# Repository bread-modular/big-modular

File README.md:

# Big Modular

A collection of Eurorack modules built with shared KiCad tooling.

## Modules

| Module | Description | Release |
| --- | --- | --- |
| [`usb-power`](modules/usb-power/) | USB-C PD input → protected 9V, dual TPS54302 bucks, TPS65131 raw ±13.5V, TPS7A4700/TPS7A3301 quiet ±12V, +5V | LDO-R1 source; recovered exports STALE |

Each module is self-contained under `modules/<name>/`:

```text
modules/usb-power/
  hardware/     KiCad project (usb-power.kicad_{pro,sch,pcb}, panel, local libs)
  docs/         design, fabrication and evidence notes
  tools/        module generators/checkers
  tests/        module regression tests
  jlcpcb/       recovered Gerber/BOM/CPL snapshot (STALE until re-export)
```

## Common tooling

`opt/` holds shared, module-independent tooling and must not be copied into modules:

- `opt/kicad-tools/` — native KiCad checks, PCB/schematic edits, JLCPCB export/assembly
- `opt/kicad-routing/` — optional router facade

Read `opt/kicad-tools/skills/kicad-workflow/SKILL.md` and
`opt/kicad-tools/skills/jlcpcb-assembly/SKILL.md` before KiCad or sourcing work.

## Quick check

```sh
python3 -B opt/kicad-tools/kicad_tools.py doctor --config modules/usb-power/tools/kicad-project.json
python3 -B -m unittest discover -s modules/usb-power/tests -v
```

Recovery evidence and remaining release gates: [`modules/usb-power/docs/migration-recovery.md`](modules/usb-power/docs/migration-recovery.md).

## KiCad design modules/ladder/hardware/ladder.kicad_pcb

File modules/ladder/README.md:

# LADDER: analog 16bit ladder filter + envelope + vactrol VCA

An analog take on the modules/16bit polysynth ladder filter: a classic Moog 4-pole
transistor ladder with the 16bit's controls and its resonance makeup (the dry level holds as
resonance goes up), an ATtiny1616 envelope driven by GATE or MIDI, a full CV bypass, and a
Bread Modular V2CA-style vactrol VCA on the filter output.

| Control / jack | Function |
|---|---|
| **CUTOFF** | ~55 Hz .. ~17 kHz, exponential, CW = open |
| **RESONANCE** | vactrol-controlled, 0 .. self-oscillation near the top (point depends on the vactrol); dry level kept (16bit (1 + k) makeup) |
| **ENV TIME** | attack = release, 5 ms .. 2 s (firmware) |
| **DEPTH** | 0 .. +8 octaves of envelope (or CV) on top of CUTOFF (read by the MCU, recordable) |
| **REC** + LED | records ENV TIME + DEPTH for 4 bars on MIDI clock, then loops (as ACID; firmware to write) |
| **CURVE** | VCA response: CCW punchy, CW soft (V2CA CURVE) |
| **MIDI**, **GATE** | start / release the envelope (MIDI: TS, JP1 protected / direct) |
| **CV** | 0..5 V, replaces the envelope (cutoff via the MCU x DEPTH; the VCA directly) |
| **AUDIO IN** | 10 Vpp |
| **RES CV** | adds to RESONANCE (slow, through the vactrol), +5 V ~ the knob's full range |
| **FILTER OUT**, **VCA OUT** | direct ladder out; through the vactrol VCA |

**Status: S3 schematic (vactrol resonance, REC; ERC 0, netlist asserted) + R2 routed carrier: 10HP,
4 layers, all SMD on the back (manual routing + 2026-11-10 fab-review fixes; DRC 0 / unconnected 0 /
parity 0). Panel PCB + printable panel. JLCPCB export in [`jlcpcb/`](jlcpcb/README.md), not
supplier-accepted, not built. No firmware.**

Panel, top to bottom: MIDI, GATE, CV, RES CV; CUTOFF, RES; ENV TIME, DEPTH; REC button + LED,
CURVE; AUDIO IN, FILTER OUT, VCA OUT.

```sh
python3 -B tools/build_schematic.py   # schematic (placement by hand, wires by its router)
python3 -B tools/build_layout.py      # carrier P2 placement + panel (refuses a routed carrier: do not run)
python3 -B tools/sim_ladder.py        # ngspice check of ladder / expo / resonance
kicad-cli sch erc --severity-all --format json -o research/erc.json hardware/ladder.kicad_sch
```

Schematic PDF: [`docs/ladder-schematic.pdf`](docs/ladder-schematic.pdf). Design notes:
[`docs/research.md`](docs/research.md).

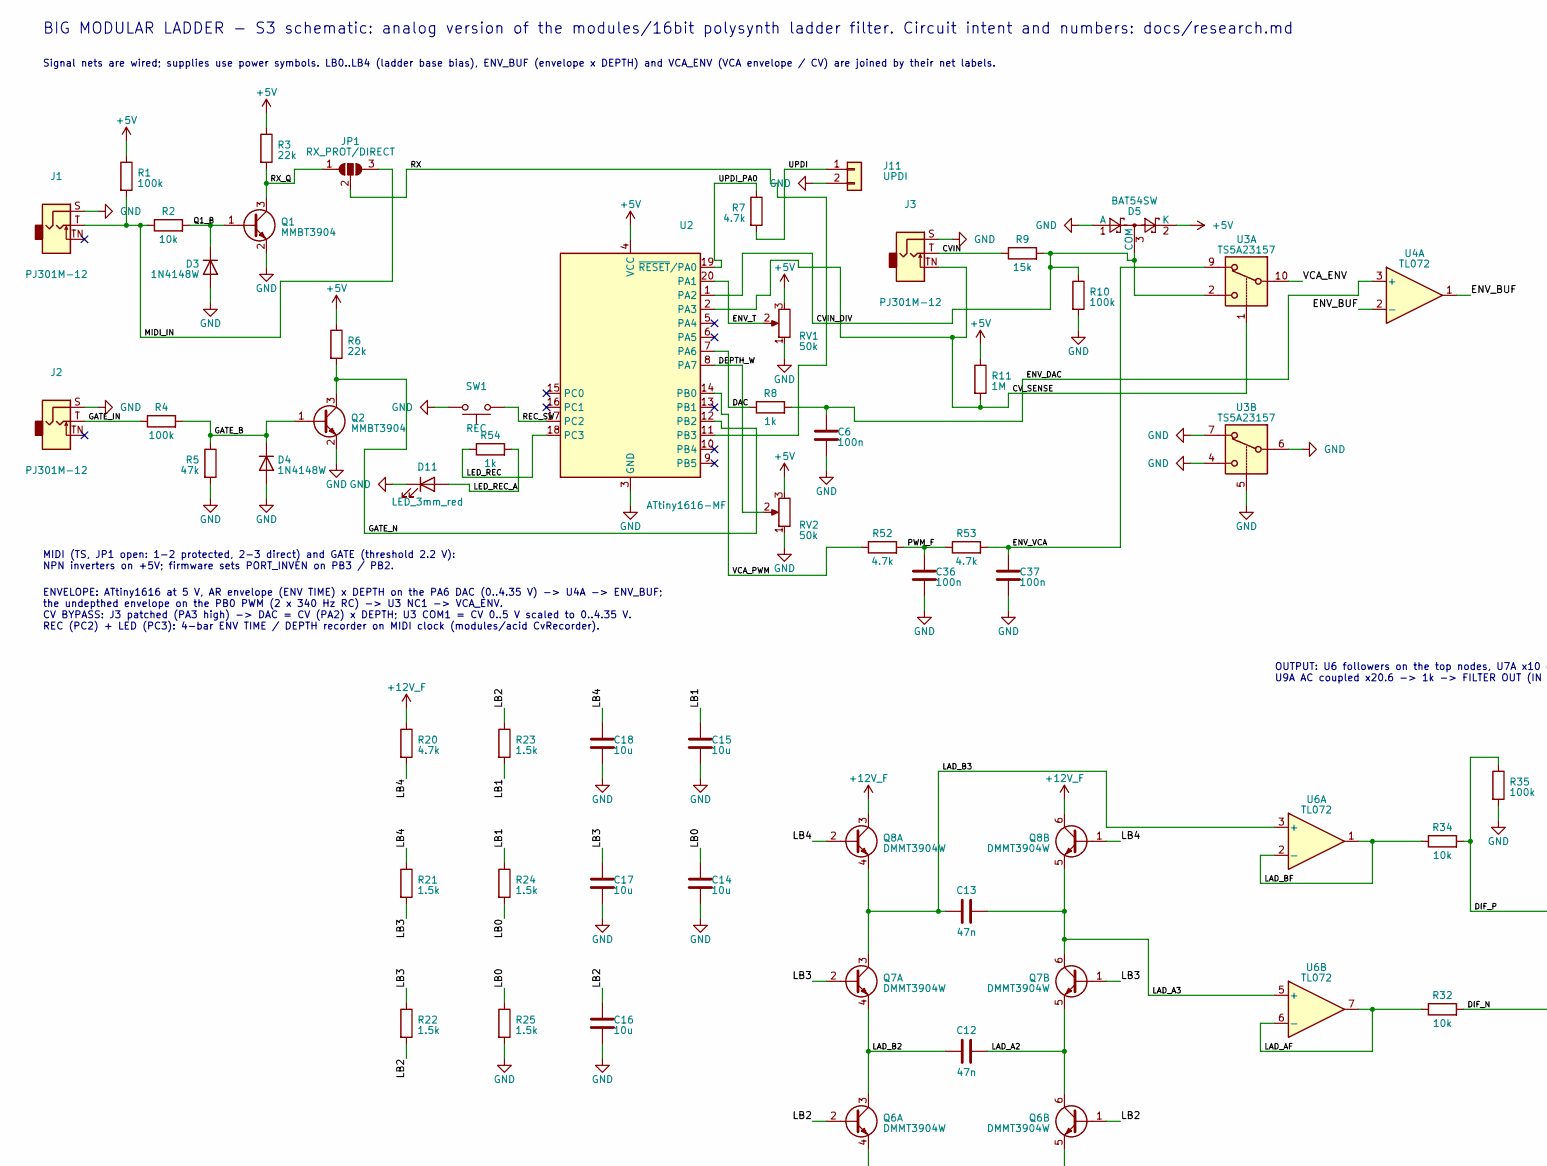
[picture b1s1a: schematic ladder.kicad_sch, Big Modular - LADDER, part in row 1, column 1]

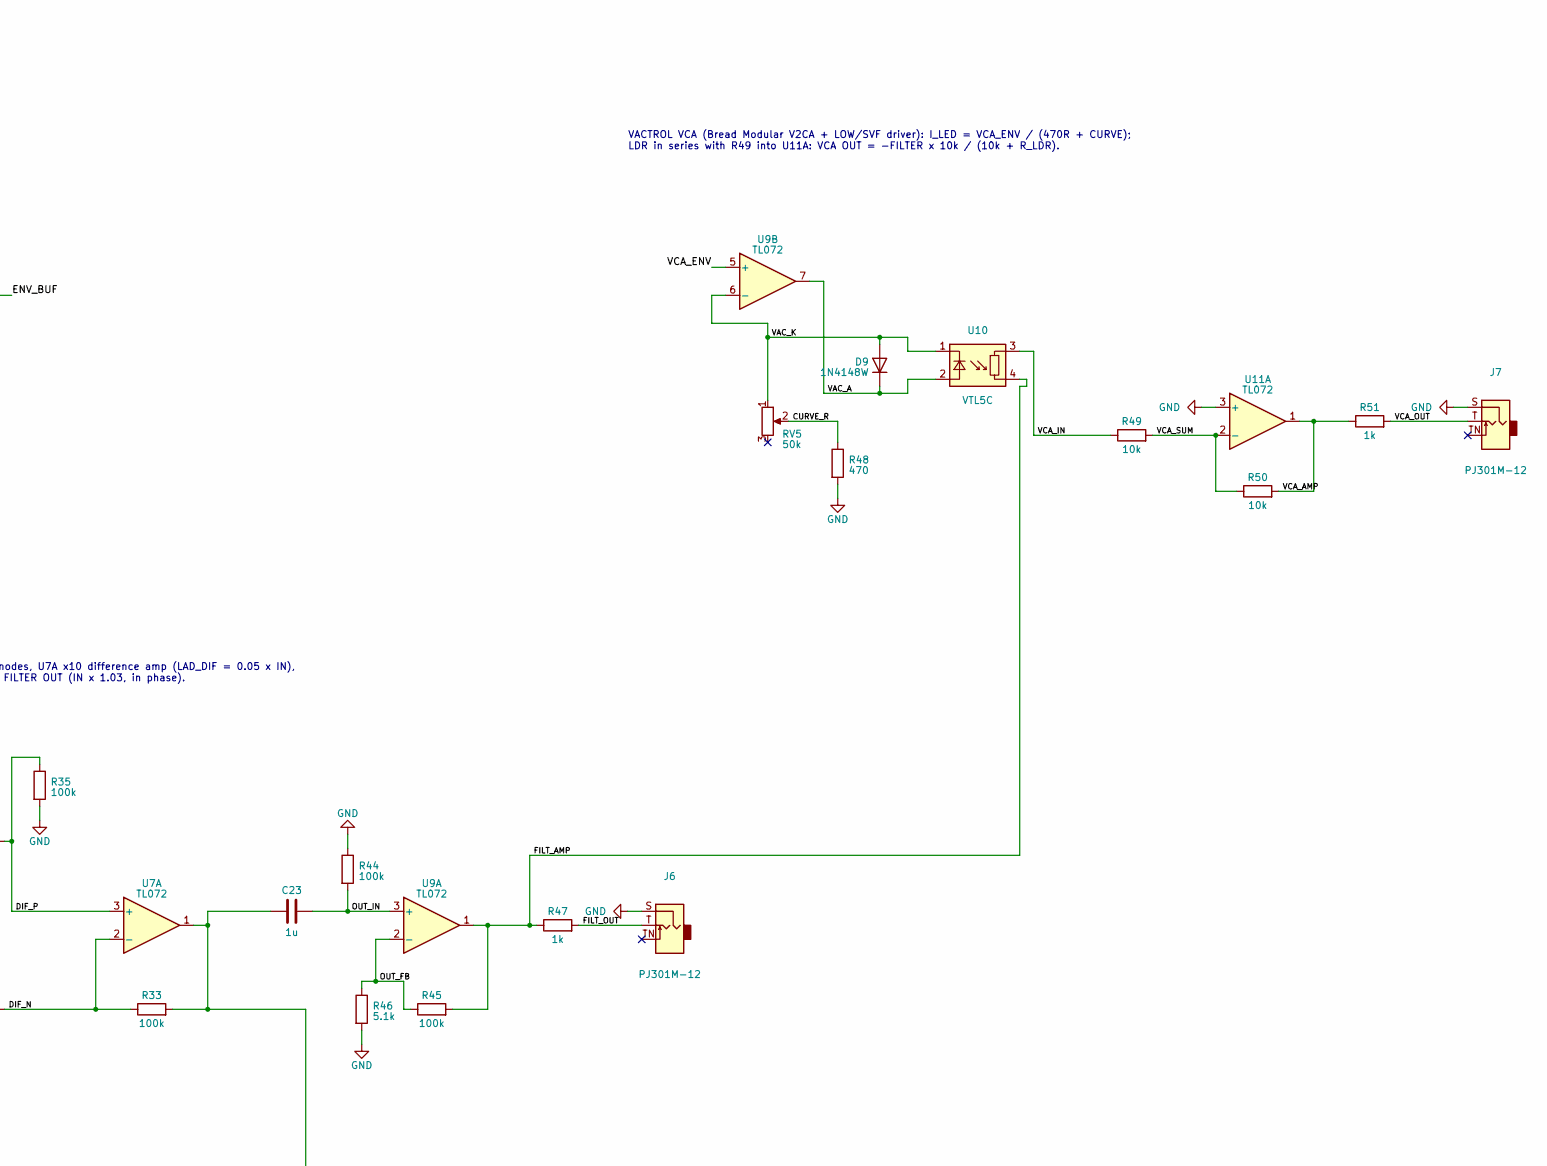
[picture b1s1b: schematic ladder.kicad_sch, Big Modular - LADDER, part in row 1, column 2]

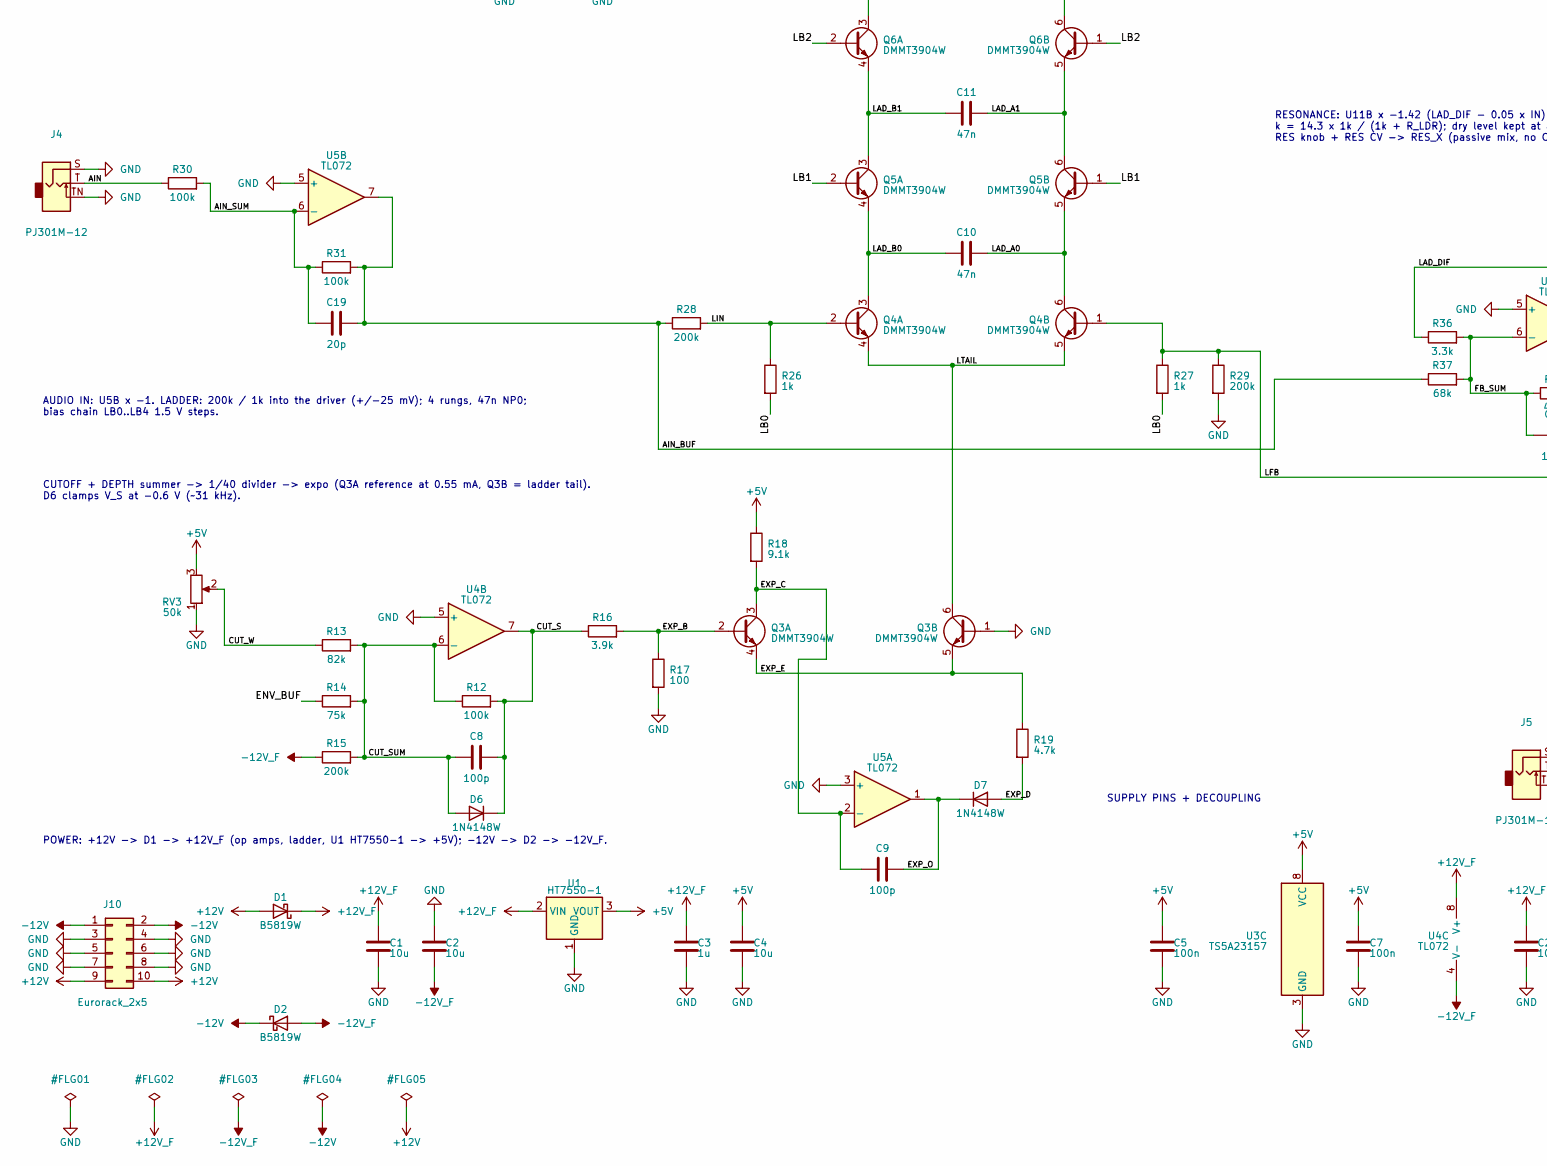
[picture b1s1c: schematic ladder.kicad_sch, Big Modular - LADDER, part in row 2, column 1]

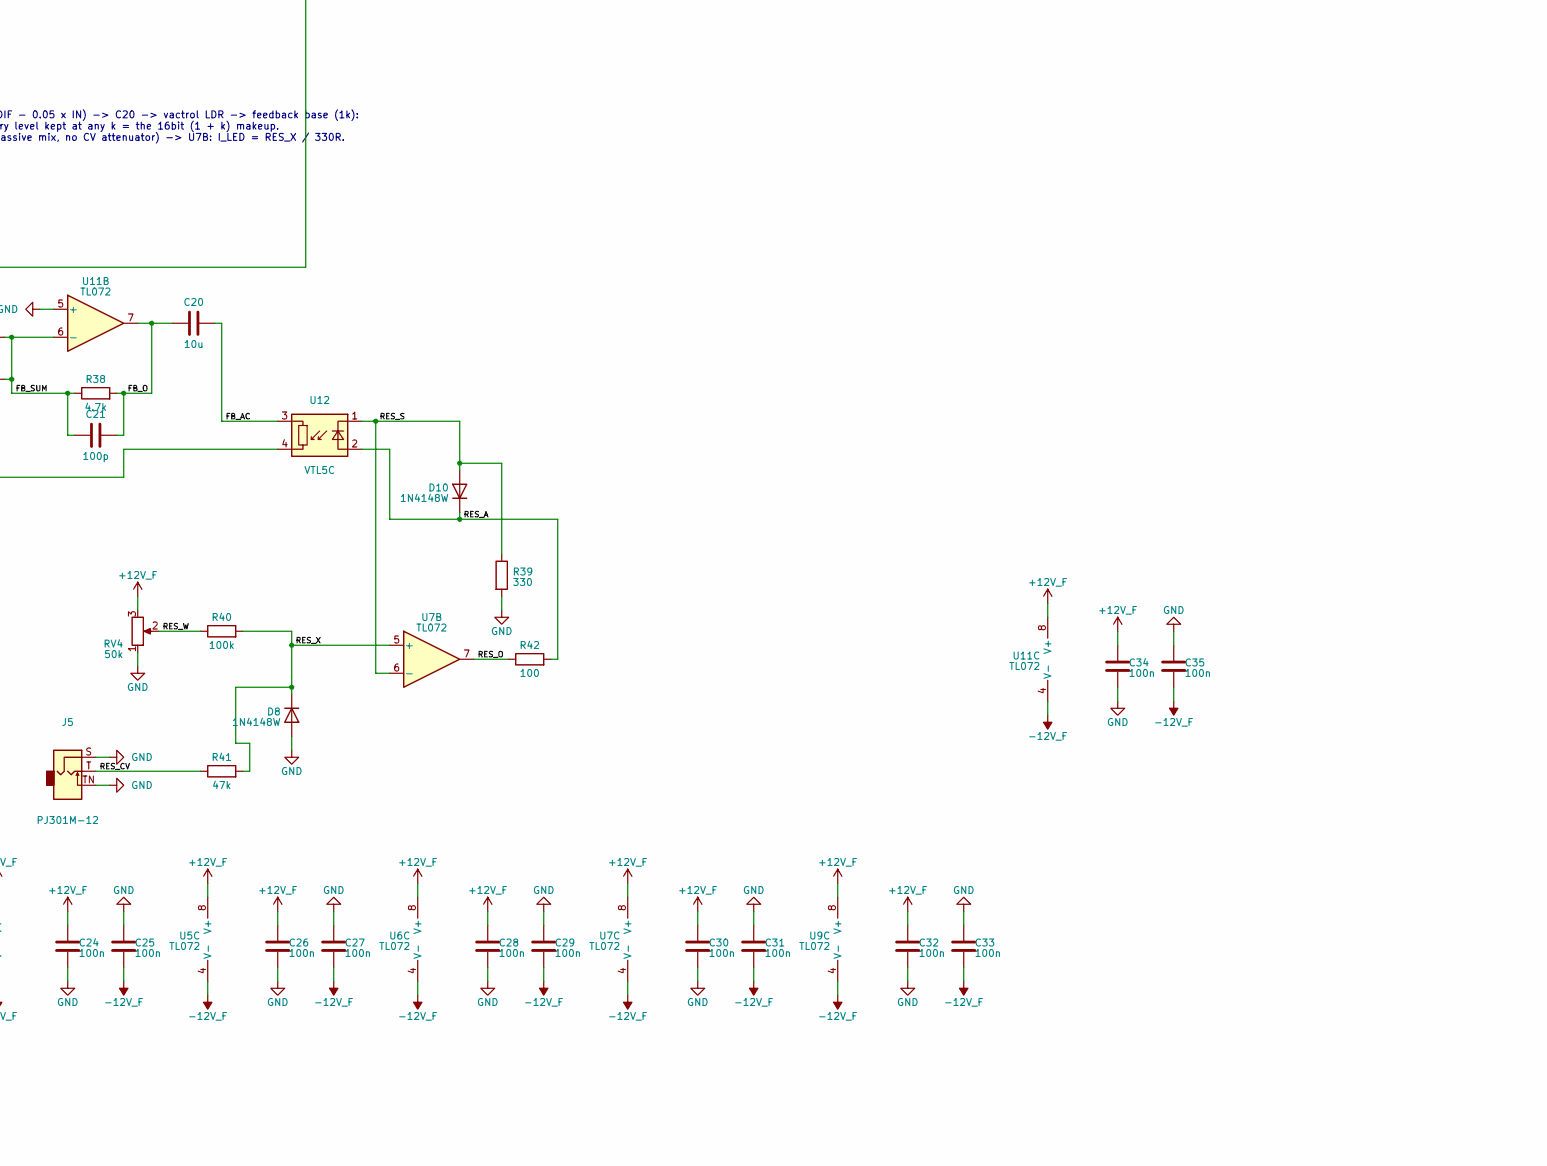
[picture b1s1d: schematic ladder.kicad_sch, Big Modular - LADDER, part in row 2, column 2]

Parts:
C1, C2, C4, C14, C15, C16, C17, C18, C20: 10u; C_0805_2012Metric; Voltage 25V; MPN CL21A106KAYNNNE; LCSC C15850
C3, C23: 1u; C_0805_2012Metric; Voltage 50V; MPN CL21B105KBFNNNE; LCSC C28323
C5, C6, C7, C24, C25, C26, C27, C28, C29, C30, C31, C32, C33, C34, C35, C36, C37: 100n; C_0603_1608Metric; Voltage 50V; MPN CC0603KRX7R9BB104; LCSC C14663
C8, C9, C21: 100p; C_0603_1608Metric; Voltage 50V; MPN CL10C101JB8NNNC; LCSC C14858
C10, C11, C12, C13: 47n; C_1206_3216Metric; Voltage 100V; MPN C1206N473J101T; LCSC C20617849
C19: 20p; C_0603_1608Metric; Voltage 50V; MPN CL10C200JB8NNNC; LCSC C1648
D1, D2: B5819W; D_SOD-123; MPN B5819W SL; LCSC C8598
D3, D4, D6, D7, D8, D9, D10: 1N4148W; D_SOD-123; MPN 1N4148W; LCSC C81598
D5: BAT54SW; SOT-323_SC-70; MPN BAT54SWT1G; LCSC C78260
D11: LED_3mm_red; LED_D3.0mm
J1, J2, J3, J4, J5, J6, J7: PJ301M-12; Jack_3.5mm_QingPu_WQP-PJ301M-12_Vertical
J10: Eurorack_2x5; PinHeader_2x05_P2.54mm_Vertical
J11: UPDI; PinHeader_1x02_P2.54mm_Vertical
JP1: RX_PROT/DIRECT; SolderJumper-3_P1.3mm_Open_RoundedPad1.0x1.5mm
Q1, Q2: MMBT3904; SOT-23; MPN MMBT3904(RANGE:100-300); LCSC C20526
Q3, Q4, Q5, Q6, Q7, Q8: DMMT3904W; SOT-363_SC-70-6; MPN DMMT3904W-7-F; LCSC C155305
R1, R4, R10, R12, R30, R31, R33, R35, R40, R44, R45: 100k; R_0603_1608Metric; MPN 0603WAF1003T5E; LCSC C25803
R2, R32, R34, R49, R50: 10k; R_0603_1608Metric; MPN 0603WAF1002T5E; LCSC C25804
R3, R6: 22k; R_0603_1608Metric; MPN 0603WAF2202T5E; LCSC C31850
R5, R41: 47k; R_0603_1608Metric; MPN 0603WAF4702T5E; LCSC C25819
R7, R19, R20, R38, R52, R53: 4.7k; R_0603_1608Metric; MPN 0603WAF4701T5E; LCSC C23162
R8, R26, R27, R54: 1k; R_0603_1608Metric; MPN 0603WAF1001T5E; LCSC C21190
R9: 15k; R_0603_1608Metric; MPN 0603WAF1502T5E; LCSC C22809
R11: 1M; R_0603_1608Metric; MPN 0603WAF1004T5E; LCSC C22935
R13: 82k; R_0603_1608Metric; MPN 0603WAF8202T5E; LCSC C23254
R14: 75k; R_0603_1608Metric; MPN 0603WAF7502T5E; LCSC C23242
R15, R28, R29: 200k; R_0603_1608Metric; MPN 0603WAF2003T5E; LCSC C25811
R16: 3.9k; R_0603_1608Metric; MPN 0603WAF3901T5E; LCSC C23018
R17, R42: 100; R_0603_1608Metric; MPN 0603WAF1000T5E; LCSC C22775
R18: 9.1k; R_0603_1608Metric; MPN 0603WAF9101T5E; LCSC C23260
R21, R22, R23, R24, R25: 1.5k; R_0603_1608Metric; MPN 0603WAF1501T5E; LCSC C22843
R36: 3.3k; R_0603_1608Metric; MPN 0603WAF3301T5E; LCSC C22978
R37: 68k; R_0603_1608Metric; MPN 0603WAF6802T5E; LCSC C23231
R39: 330; R_0603_1608Metric; MPN 0603WAF3300T5E; LCSC C23138
R46: 5.1k; R_0603_1608Metric; MPN 0603WAF5101T5E; LCSC C23186
R47, R51: 1k; R_1206_3216Metric; MPN ESR18EZPF1001; LCSC C2074262
R48: 470; R_0603_1608Metric; MPN 0603WAF4700T5E; LCSC C23179
RV1, RV2, RV3, RV4, RV5: 50k; Potentiometer_RV09
SW1: REC; SW_PUSH_6mm_H7.3mm; MPN 6x6x7 mm THT tact switch, 4 pins (gener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
U1: HT7550-1; SOT-89-3; MPN HT7550-1; LCSC C16106
U2: ATtiny1616-MF; VQFN-20-1EP_3x3mm_P0.4mm_EP1.7x1.7mm; MPN ATTINY1616-MF; LCSC C5227638
U3: TS5A23157; TSSOP-10_3x3mm_P0.5mm; MPN TS5A23157DGSR; LCSC C11133
U4, U5, U6, U7, U9, U11: TL072; SOIC-8_3.9x4.9mm_P1.27mm; MPN TL072CDT; LCSC C6961
U10, U12: VTL5C

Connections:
+5V: C4.1, C5.1, C7.1, D5.2 (K), R1.1, R3.1, R6.1, R11.1, R18.1, RV1.3, RV2.3, RV3.3, U1.3 (VOUT), U2.4 (VCC), U3.8 (VCC)
+12V: D1.2 (A), J10.9, J10.10
+12V_F: C1.1, C3.1, C24.1, C26.1, C28.1, C30.1, C32.1, C34.1, D1.1 (K), Q8.3 (C1), Q8.6 (C2), R20.1, RV4.3, U1.2 (VIN), U4.8 (V+), U5.8 (V+), U6.8 (V+), U7.8 (V+), U9.8 (V+), U11.8 (V+)
-12V: D2.1 (K), J10.1, J10.2
-12V_F: C2.2, C25.2, C27.2, C29.2, C31.2, C33.2, C35.2, D2.2 (A), R15.1, U4.4 (V-), U5.4 (V-), U6.4 (V-), U7.4 (V-), U9.4 (V-), U11.4 (V-)
/AIN: J4.T, R30.1
/AIN_BUF: C19.2, R28.1, R31.2, R37.1, U5.7
/AIN_SUM: C19.1, R30.2, R31.1, U5.6 (-)
/CURVE_R: R48.1, RV5.2
/CUT_S: C8.2, D6.1 (K), R12.2, R16.1, U4.7
/CUT_SUM: C8.1, D6.2 (A), R12.1, R13.2, R14.2, R15.2, U4.6 (-)
/CUT_W: R13.1, RV3.2
/CVIN: J3.T, R9.1
/CVIN_DIV: D5.3 (COM), R9.2, R10.1, U2.1 (PA2), U3.2
/CV_SENSE: J3.TN, R11.2, U2.2 (PA3), U3.1
/DAC: R8.1, U2.7 (PA6)
/DEPTH_W: RV2.2, U2.8 (PA7)
/DIF_N: R32.2, R33.1, U7.2 (-)
/DIF_P: R34.2, R35.1, U7.3 (+)
/ENV_BUF: R14.1, U4.1, U4.2 (-)
/ENV_DAC: C6.1, R8.2, U4.3 (+)
/ENV_T: RV1.2, U2.20 (PA1)
/ENV_VCA: C37.1, R53.2, U3.9
/EXP_B: Q3.2 (B1), R16.2, R17.1
/EXP_C: C9.1, Q3.3 (C1), R18.2, U5.2 (-)
/EXP_D: D7.2 (A), R19.2
/EXP_E: Q3.4 (E1), Q3.5 (E2), R19.1
/EXP_O: C9.2, D7.1 (K), U5.1
/FB_AC: C20.2, U12.3
/FB_O: C20.1, C21.2, R38.2, U11.7
/FB_SUM: C21.1, R36.2, R37.2, R38.1, U11.6 (-)
/FILT_AMP: R45.2, R47.1, U9.1, U10.4
/FILT_OUT: J6.T, R47.2
/GATE_B: D4.1 (K), Q2.1 (B), R4.2, R5.1
/GATE_IN: J2.T, R4.1
/GATE_N: Q2.3 (C), R6.2, U2.12 (PB2)
/LAD_A0: C10.2, Q4.6 (C2), Q5.5 (E2)
/LAD_A1: C11.2, Q5.6 (C2), Q6.5 (E2)
/LAD_A2: C12.2, Q6.6 (C2), Q7.5 (E2)
/LAD_A3: C13.2, Q7.6 (C2), Q8.5 (E2), U6.5 (+)
/LAD_AF: R32.1, U6.6 (-), U6.7
/LAD_B0: C10.1, Q4.3 (C1), Q5.4 (E1)
/LAD_B1: C11.1, Q5.3 (C1), Q6.4 (E1)
/LAD_B2: C12.1, Q6.3 (C1), Q7.4 (E1)
/LAD_B3: C13.1, Q7.3 (C1), Q8.4 (E1), U6.3 (+)
/LAD_BF: R34.1, U6.1, U6.2 (-)
/LAD_DIF: C23.1, R33.2, R36.1, U7.1
/LB0: C14.1, R24.2, R25.1, R26.2, R27.2
/LB1: C15.1, Q5.1 (B2), Q5.2 (B1), R23.2, R24.1
/LB2: C16.1, Q6.1 (B2), Q6.2 (B1), R22.2, R23.1
/LB3: C17.1, Q7.1 (B2), Q7.2 (B1), R21.2, R22.1
/LB4: C18.1, Q8.1 (B2), Q8.2 (B1), R20.2, R21.1
/LED_REC: R54.1, U2.18 (PC3)
/LED_REC_A: D11.2 (A), R54.2
/LFB: Q4.1 (B2), R27.1, R29.1, U12.4
/LIN: Q4.2 (B1), R26.1, R28.2
/LTAIL: Q3.6 (C2), Q4.4 (E1), Q4.5 (E2)
/MIDI_IN: J1.T, JP1.3 (B), R1.2, R2.1
/OUT_FB: R45.1, R46.1, U9.2 (-)
/OUT_IN: C23.2, R44.2, U9.3 (+)
/PWM_F: C36.1, R52.2, R53.1
/Q1_B: D3.1 (K), Q1.1 (B), R2.2
/REC_SW: SW1.1, U2.17 (PC2)
/RES_A: D10.1 (K), R42.2, U12.2 (+)
/RES_CV: J5.T, R41.1
/RES_O: R42.1, U7.7
/RES_S: D10.2 (A), R39.1, U7.6 (-), U12.1 (-)
/RES_W: R40.1, RV4.2
/RES_X: D8.1 (K), R40.2, R41.2, U7.5 (+)
/RX: JP1.2 (C), U2.11 (PB3)
/RX_Q: JP1.1 (A), Q1.3 (C), R3.2
/UPDI: J11.1, R7.2
/UPDI_PA0: R7.1, U2.19 (~RESET/PA0)
/VAC_A: D9.1 (K), U9.7, U10.2 (+)
/VAC_K: D9.2 (A), RV5.1, U9.6 (-), U10.1 (-)
/VCA_AMP: R50.2, R51.1, U11.1
/VCA_ENV: U3.10, U9.5 (+)
/VCA_IN: R49.1, U10.3
/VCA_OUT: J7.T, R51.2
/VCA_PWM: R52.1, U2.14 (PB0)
/VCA_SUM: R49.2, R50.1, U11.2 (-)
GND: C1.2, C2.1, C3.2, C4.2, C5.2, C6.2, C7.2, C14.2, C15.2, C16.2, C17.2, C18.2, C24.2, C25.1, C26.2, C27.1, C28.2, C29.1, C30.2, C31.1, C32.2, C33.1, C34.2, C35.1, C36.2, C37.2, D3.2 (A), D4.2 (A), D5.1 (A), D8.2 (A), D11.1 (K), J1.S, J2.S, J3.S, J4.S, J4.TN, J5.S, J5.TN, J6.S, J7.S, J10.3, J10.4, J10.5, J10.6, J10.7, J10.8, J11.2, Q1.2 (E), Q2.2 (E), Q3.1 (B2), R5.2, R10.2, R17.2, R25.2, R29.2, R35.2, R39.2, R44.1, R46.2, R48.2, RV1.1, RV2.1, RV3.1, RV4.1, SW1.2, U1.1 (GND), U2.3 (GND), U2.21 (GND), U3.3 (GND), U3.4, U3.5, U3.6, U3.7, U4.5 (+), U5.3 (+), U5.5 (+), U11.3 (+), U11.5 (+)

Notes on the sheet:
MIDI (TS, JP1 open: 1-2 protected, 2-3 direct) and GATE (threshold 2.2 V): NPN inverters on +5V; firmware sets PORT_INVEN on PB3 / PB2.
BIG MODULAR LADDER - S3 schematic: analog version of the modules/16bit polysynth ladder filter. Circuit intent and numbers: docs/research.md
ENVELOPE: ATtiny1616 at 5 V, AR envelope (ENV TIME) x DEPTH on the PA6 DAC (0..4.35 V) -> U4A -> ENV_BUF; the undepthed envelope on the PB0 PWM (2 x 340 Hz RC) -> U3 NC1 -> VCA_ENV. CV BYPASS: J3 patched (PA3 high) -> DAC = CV (PA2) x DEPTH; U3 COM1 = CV 0..5 V scaled to 0..4.35 V. REC (PC2) + LED 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
Signal nets are wired; supplies use power symbols. LB0..LB4 (ladder base bias), ENV_BUF (envelope x DEPTH) and VCA_ENV (VCA envelope / CV) are joined by their net labels.
AUDIO IN: U5B x -1. LADDER: 200k / 1k into the driver (+/-25 mV); 4 rungs, 47n NP0; bias chain LB0..LB4 1.5 V steps.
RESONANCE: U11B x -1.42 (LAD_DIF - 0.05 x IN) -> C20 -> vactrol LDR -> feedback base (1k): k = 14.3 x 1k / (1k + R_LDR); dry level kept at any k = the 16bit (1 + k) makeup. RES knob + RES CV -> RES_X (passive mix, no CV attenuator) -> U7B: I_LED = RES_X / 330R.
POWER: +12V -> D1 -> +12V_F (op amps, ladder, U1 HT7550-1 -> +5V); -12V -> D2 -> -12V_F.
SUPPLY PINS + DECOUPLING
OUTPUT: U6 followers on the top nodes, U7A x10 difference amp (LAD_DIF = 0.05 x IN), U9A AC coupled x20.6 -> 1k -> FILTER OUT (IN x 1.03, in phase).
VACTROL VCA (Bread Modular V2CA + LOW/SVF driver): I_LED = VCA_ENV / (470R + CURVE); LDR in series with R49 into U11A: VCA OUT = -FILTER x 10k / (10k + R_LDR).
CUTOFF + DEPTH summer -> 1/40 divider -> expo (Q3A reference at 0.55 mA, Q3B = ladder tail). D6 clamps V_S at -0.6 V (~31 kHz).

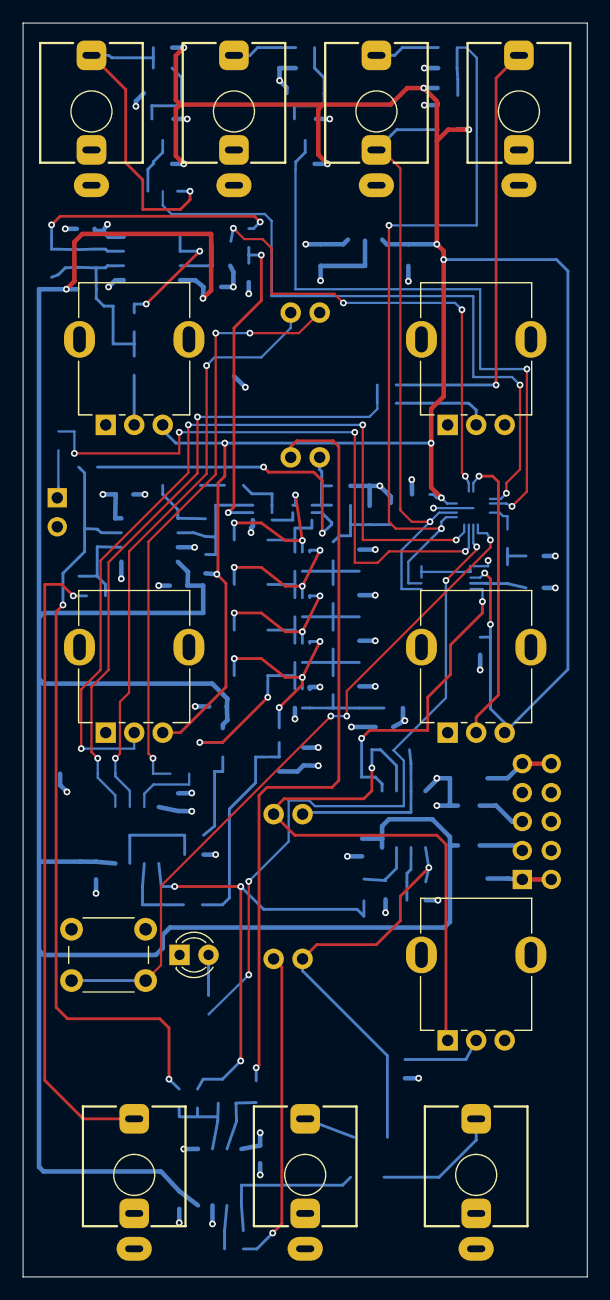
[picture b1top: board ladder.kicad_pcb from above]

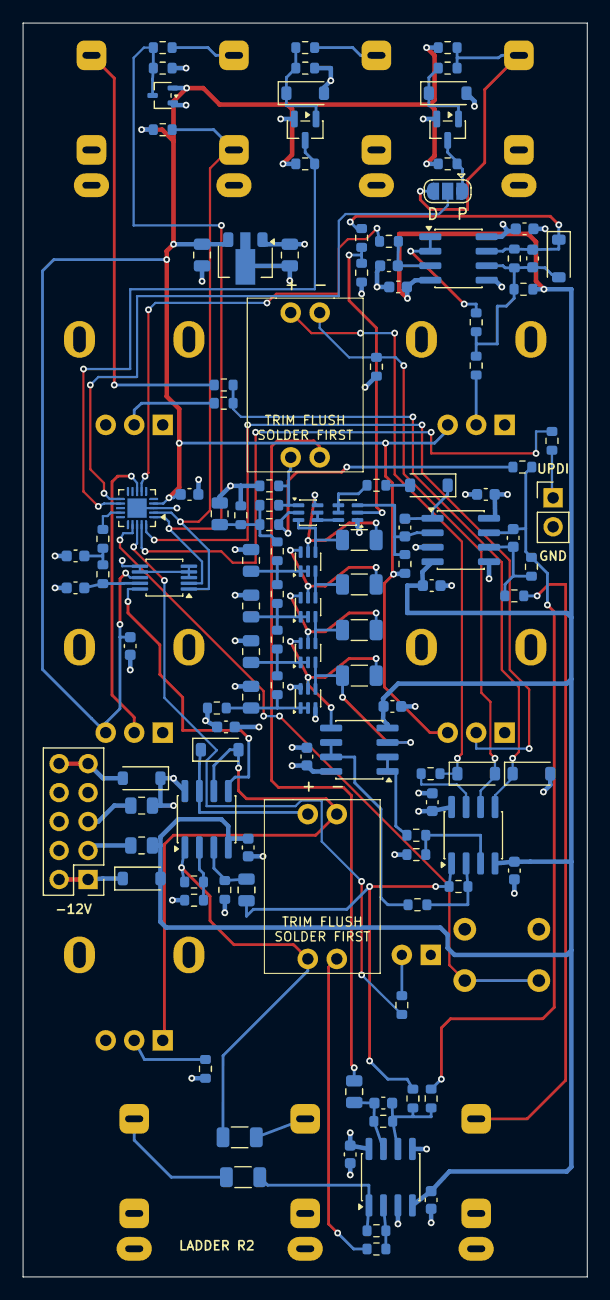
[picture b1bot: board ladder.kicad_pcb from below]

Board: 4 copper layers, 49.5 x 110.0 mm, 135 parts (121 on the bottom side), 82 nets.
